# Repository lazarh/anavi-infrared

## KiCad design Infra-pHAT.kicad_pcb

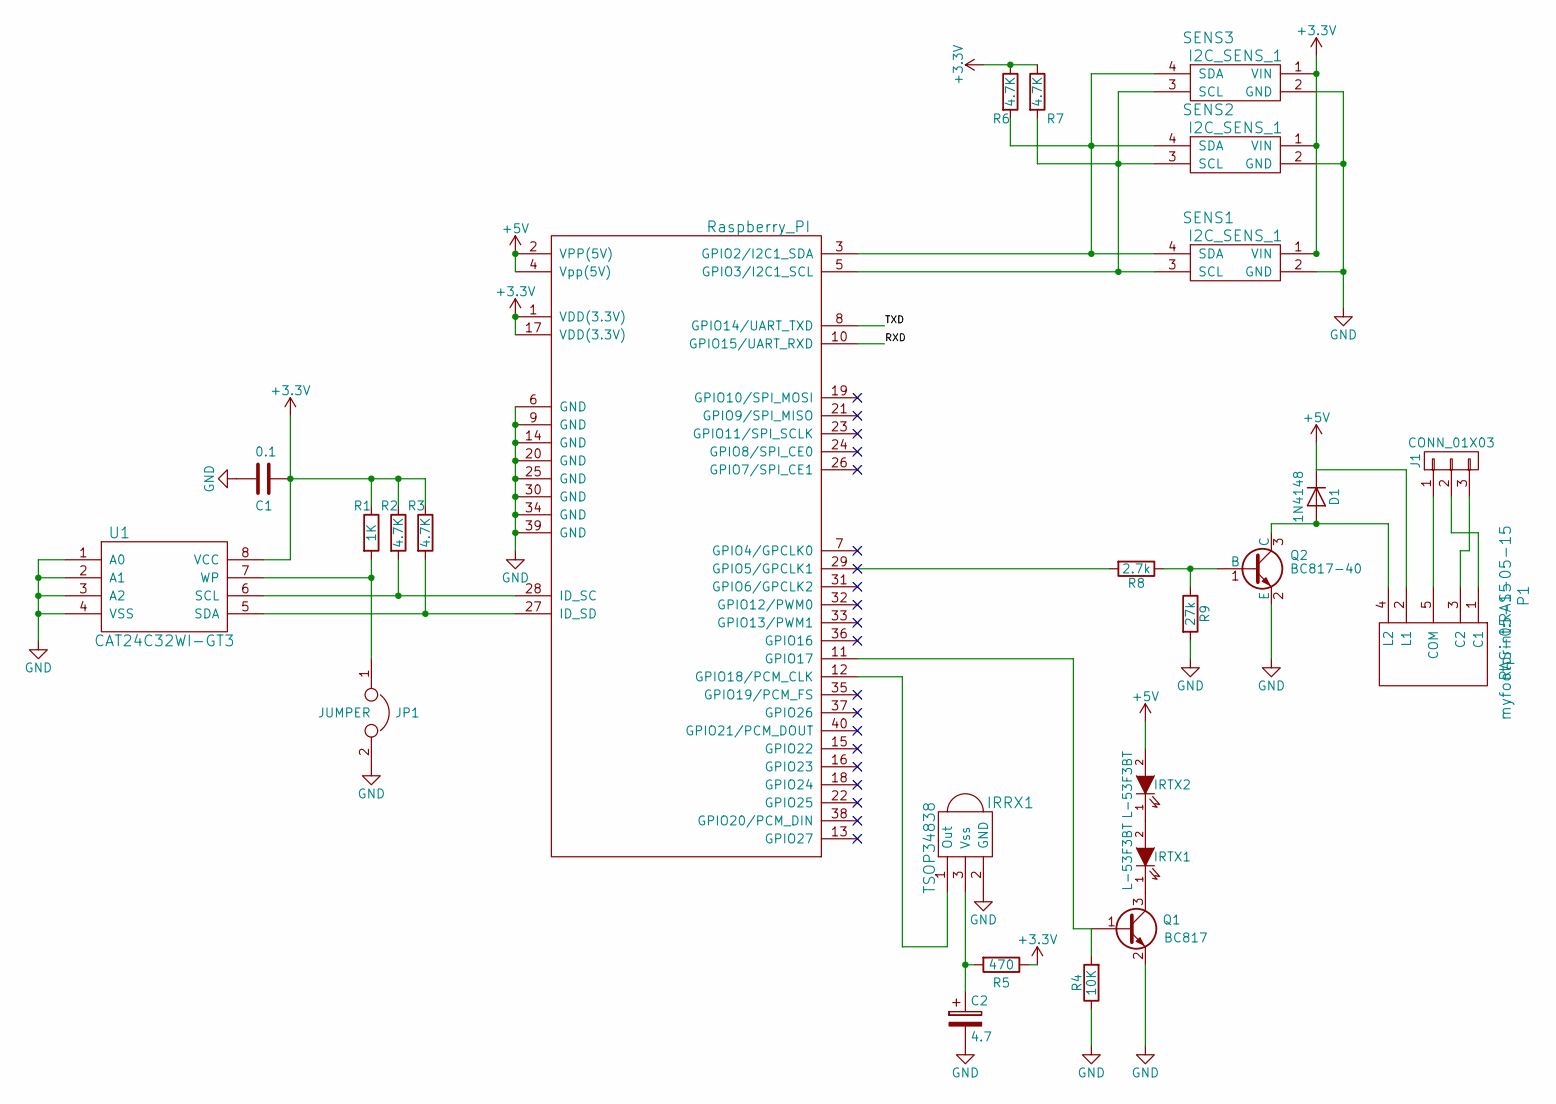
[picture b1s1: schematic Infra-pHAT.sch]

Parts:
C1: 0.1; C_0603_HandSoldering
C2: 4.7; C_0805_HandSoldering
D1: 1N4148; D_SOD-123
IRRX1: TSOP34838; TSOP38X
IRTX1, IRTX2: L-53F3BT; LED_D5.0mm
J1: CONN_01X03; KLEMA_1x3
JP1: JUMPER; Pin_Header_Straight_1x02_Pitch1.00mm
P1: RAS-05-15
Q1: BC817; SOT-23
Q2: BC817-40; SOT-23
R1: 1K; R_0603_HandSoldering
R2, R3, R6, R7: 4.7K; R_0603_HandSoldering
R4: 10K; R_0603_HandSoldering
R5: 470; R_0603_HandSoldering
R8: 2.7k; R_0603_HandSoldering
R9: 27k; R_0603_HandSoldering
RASP_CONN1: Raspberry_PI; Pin_Header_Straight_2x20
SENS1, SENS2, SENS3: I2C_SENS_1; Pin_Header_Straight_1x04_Pitch1.00mm
U1: CAT24C32WI-GT3; DIP-8_W7.62mm

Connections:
+3V3: C1.1, R1.1, R2.1, R3.1, R5.1, R6.1, R7.1, RASP_CONN1.1 (VDD(3.3V)), RASP_CONN1.17 (VDD(3.3V)), SENS1.1 (VIN), SENS2.1 (VIN), SENS3.1 (VIN), U1.8 (VCC)
+5V: D1.1 (K), IRTX2.2 (A), P1.2 (L1), RASP_CONN1.2 (VPP(5V)), RASP_CONN1.4 (Vpp(5V))
/RXD: RASP_CONN1.10 (GPIO15/UART_RXD)
/TXD: RASP_CONN1.8 (GPIO14/UART_TXD)
GND: C1.2, C2.2, IRRX1.2 (GND), JP1.2, Q1.2 (E), Q2.2 (E), R4.1, R9.2, RASP_CONN1.6 (GND), RASP_CONN1.9 (GND), RASP_CONN1.14 (GND), RASP_CONN1.20 (GND), RASP_CONN1.25 (GND), RASP_CONN1.30 (GND), RASP_CONN1.34 (GND), RASP_CONN1.39 (GND), SENS1.2 (GND), SENS2.2 (GND), SENS3.2 (GND), U1.1 (A0), U1.2 (A1), U1.3 (A2), U1.4 (VSS)
unnamed: C2.1, IRRX1.3 (Vss), R5.2
unnamed: D1.2 (A), P1.4 (L2), Q2.3 (C)
unnamed: IRRX1.1 (Out), RASP_CONN1.12 (GPIO18/PCM_CLK)
unnamed: IRTX1.1 (K), Q1.3 (C)
unnamed: IRTX1.2 (A), IRTX2.1 (K)
unnamed: J1.1, P1.5 (COM)
unnamed: J1.2, P1.1 (C1)
unnamed: J1.3, P1.3 (C2)
unnamed: JP1.1, R1.2, U1.7 (WP)
unnamed: Q1.1 (B), R4.2, RASP_CONN1.11 (GPIO17)
unnamed: Q2.1 (B), R8.1, R9.1
unnamed: R2.2, RASP_CONN1.28 (ID_SC), U1.6 (SCL)
unnamed: R3.2, RASP_CONN1.27 (ID_SD), U1.5 (SDA)
unnamed: R6.2, RASP_CONN1.3 (GPIO2/I2C1_SDA), SENS1.4 (SDA), SENS2.4 (SDA), SENS3.4 (SDA)
unnamed: R7.2, RASP_CONN1.5 (GPIO3/I2C1_SCL), SENS1.3 (SCL), SENS2.3 (SCL), SENS3.3 (SCL)
unnamed: R8.2, RASP_CONN1.29 (GPIO5/GPCLK1)

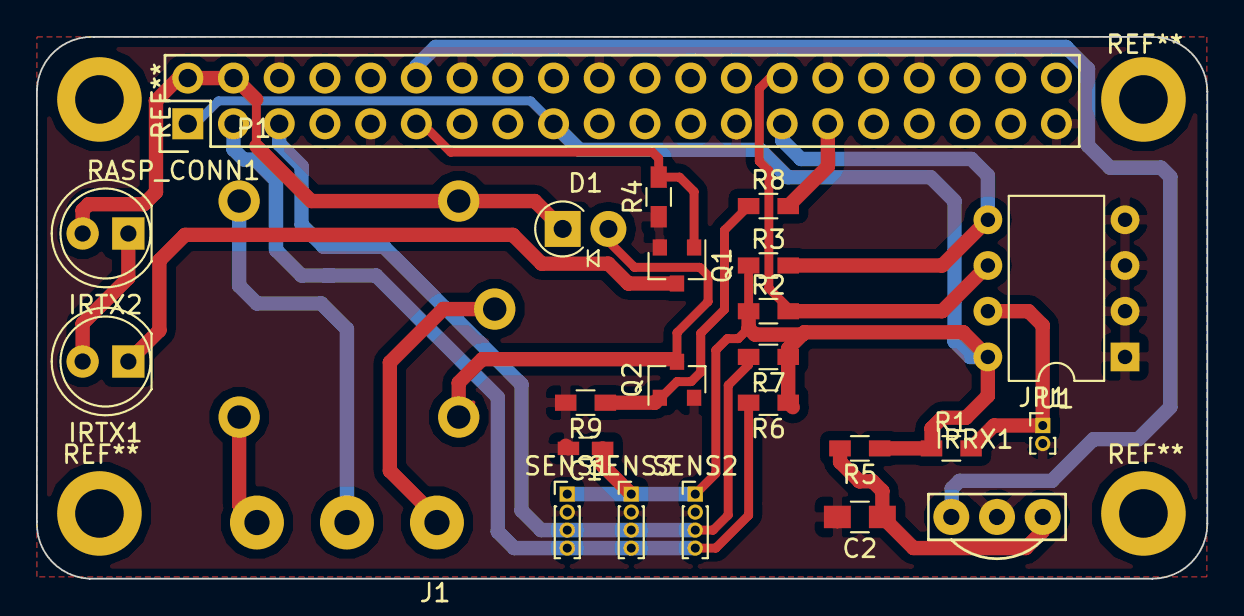
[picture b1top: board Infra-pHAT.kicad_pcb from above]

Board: 2 copper layers, 65.0 x 30.1 mm, 25 parts (0 on the bottom side), 19 nets.

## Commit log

2017-10-15 Initial version SCH + PCM
2017-10-16 Updated PCB with better tracks and oshpark kicad rules
2017-10-16 Fix on back layer GND25-30 pin
2017-10-26 PCB v1.1
